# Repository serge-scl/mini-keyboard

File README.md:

# Mouse Keyboard Pyramids (MKP)

Hybrid mouse + keyboard using pyramid-shaped touch/tilt keys. MKP combines capacitive touch, tilt sensing, and small-form HID firmware to provide an alternative input device for typing and pointing.

## Features
- Pyramid-shaped keys: touch shows cursor location; tilt selects symbols/directions.
- Position sensing: MPR121 capacitive touch controller (per-pyramid address).
- Tilt sensing: magnet-mounted mesh + Hall sensors detect X/Y tilt.
- Keyboard: 5×3 matrix (with diodes) + two dedicated joystick inputs.
- Pointing: optional optical sensor (PMW3360) and two side scroll wheels (one per side).
- Modular hardware: removable side modules with 4×AA battery holders and PCBs; LED backlight PCB under keyboard.
- Assembly designed for minimal tools; partly tool-free disassembly.
- Wireless option: Raspberry Pi Pico (or Pico W for Wi‑Fi); CircuitPython with Adafruit libraries and HID support.

## Software & Files
- CircuitPython code and example text editor included in repo root (Python).
- FreeCAD (part/assembly) models and KiCad schematics/PCB in respective folders.
- Datasheet folder contains BOM, diagrams, and images.

## License
CC‑BY‑4.0

## Contact
Serge Sokolov — sergesclv@gmail.com / sergesclv3@protonmail.com

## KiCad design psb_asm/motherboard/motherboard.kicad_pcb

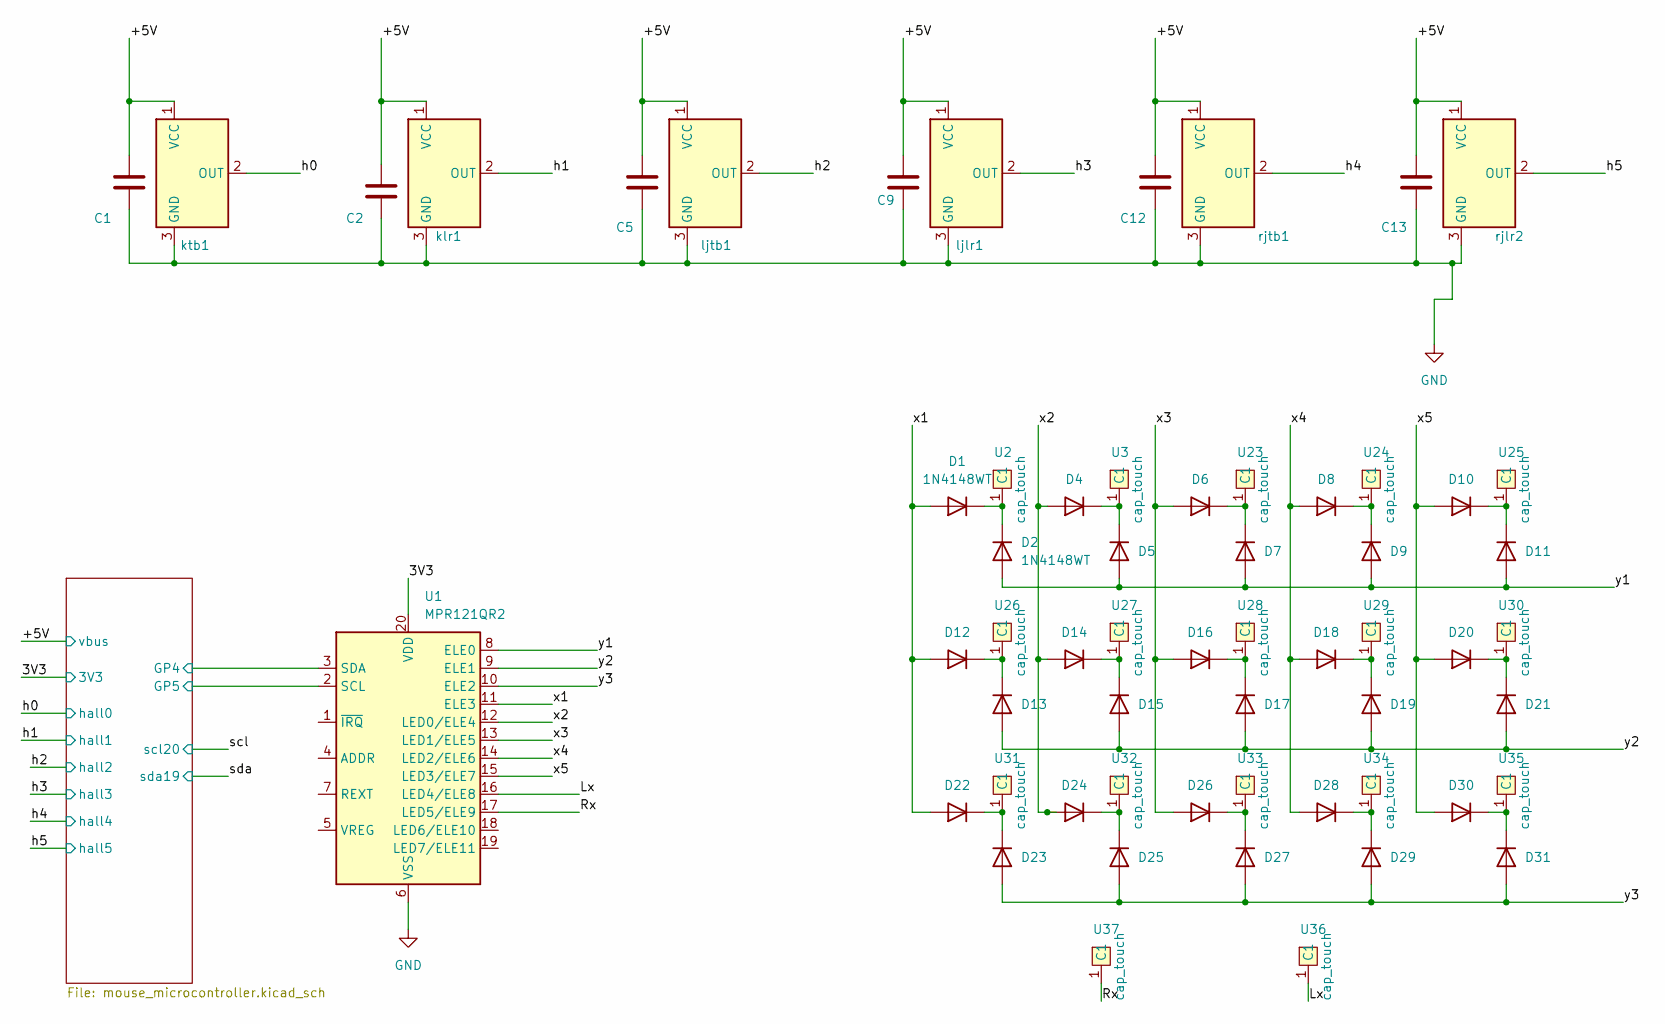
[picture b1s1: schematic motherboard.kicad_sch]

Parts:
C1, C2, C5, C9, C12, C13: 0.01uf; CP_EIA-1608-08_AVX-J_Pad1.25x1.05mm_HandSolder
D1, D2, D4, D5, D6, D7, D8, D9, D10, D11, D12, D13, D14, D15, D16, D17, D18, D19, D20, D21, D22, D23, D24, D25, D26, D27, D28, D29, D30, D31: 1N4148WT; D_SOD-523
U1: MPR121QR2; UQFN-20_3x3mm_P0.4mm
U2, U3, U23, U24, U25, U26, U27, U28, U29, U30, U31, U32, U33, U34, U35, U36, U37: cap_touch
klr1: TO-92S
ktb1: TO-92S
ljlr1: DRV505; TO-92S
ljtb1: DRV505; TO-92S
rjlr2: DRV505; TO-92S
rjtb1: DRV505; TO-92S

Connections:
/3V3: U1.20 (VDD); also elsewhere on the board
/+5V: C1.1, C2.1, C5.1, C9.1, C12.1, C13.1, klr1.1 (VCC), ktb1.1 (VCC), ljlr1.1 (VCC), ljtb1.1 (VCC), rjlr2.1 (VCC), rjtb1.1 (VCC); also elsewhere on the board
/Lx: U1.16 (LED4/ELE8), U36.1 (C1)
/Mouse_and_microcontroller/GP4: U1.3 (SDA); also elsewhere on the board
/Mouse_and_microcontroller/GP5: U1.2 (SCL); also elsewhere on the board
/Rx: U1.17 (LED5/ELE9), U37.1 (C1)
/h0: ktb1.2 (OUT); also elsewhere on the board
/h1: klr1.2 (OUT); also elsewhere on the board
/h2: ljtb1.2 (OUT); also elsewhere on the board
/h3: ljlr1.2 (OUT); also elsewhere on the board
/h4: rjtb1.2 (OUT); also elsewhere on the board
/h5: rjlr2.2 (OUT); also elsewhere on the board
/x1: D1.2 (A), D12.2 (A), D22.2 (A), U1.11 (ELE3)
/x2: D4.2 (A), D14.2 (A), D24.2 (A), U1.12 (LED0/ELE4)
/x3: D6.2 (A), D16.2 (A), D26.2 (A), U1.13 (LED1/ELE5)
/x4: D8.2 (A), D18.2 (A), D28.2 (A), U1.14 (LED2/ELE6)
/x5: D10.2 (A), D20.2 (A), D30.2 (A), U1.15 (LED3/ELE7)
/y1: D2.2 (A), D5.2 (A), D7.2 (A), D9.2 (A), D11.2 (A), U1.8 (ELE0)
/y2: D13.2 (A), D15.2 (A), D17.2 (A), D19.2 (A), D21.2 (A), U1.9 (ELE1)
/y3: D23.2 (A), D25.2 (A), D27.2 (A), D29.2 (A), D31.2 (A), U1.10 (ELE2)
GND: C1.2, C2.2, C5.2, C9.2, C12.2, C13.2, U1.6 (VSS), klr1.3 (GND), ktb1.3 (GND), ljlr1.3 (GND), ljtb1.3 (GND), rjlr2.3 (GND), rjtb1.3 (GND); also elsewhere on the board
unnamed: D1.1 (K), D2.1 (K), U2.1 (C1)
unnamed: D4.1 (K), D5.1 (K), U3.1 (C1)
unnamed: D6.1 (K), D7.1 (K), U23.1 (C1)
unnamed: D8.1 (K), D9.1 (K), U24.1 (C1)
unnamed: D10.1 (K), D11.1 (K), U25.1 (C1)
unnamed: D12.1 (K), D13.1 (K), U26.1 (C1)
unnamed: D14.1 (K), D15.1 (K), U27.1 (C1)
unnamed: D16.1 (K), D17.1 (K), U28.1 (C1)
unnamed: D18.1 (K), D19.1 (K), U29.1 (C1)
unnamed: D20.1 (K), D21.1 (K), U30.1 (C1)
unnamed: D22.1 (K), D23.1 (K), U31.1 (C1)
unnamed: D24.1 (K), D25.1 (K), U32.1 (C1)
unnamed: D26.1 (K), D27.1 (K), U33.1 (C1)
unnamed: D28.1 (K), D29.1 (K), U34.1 (C1)
unnamed: D30.1 (K), D31.1 (K), U35.1 (C1)

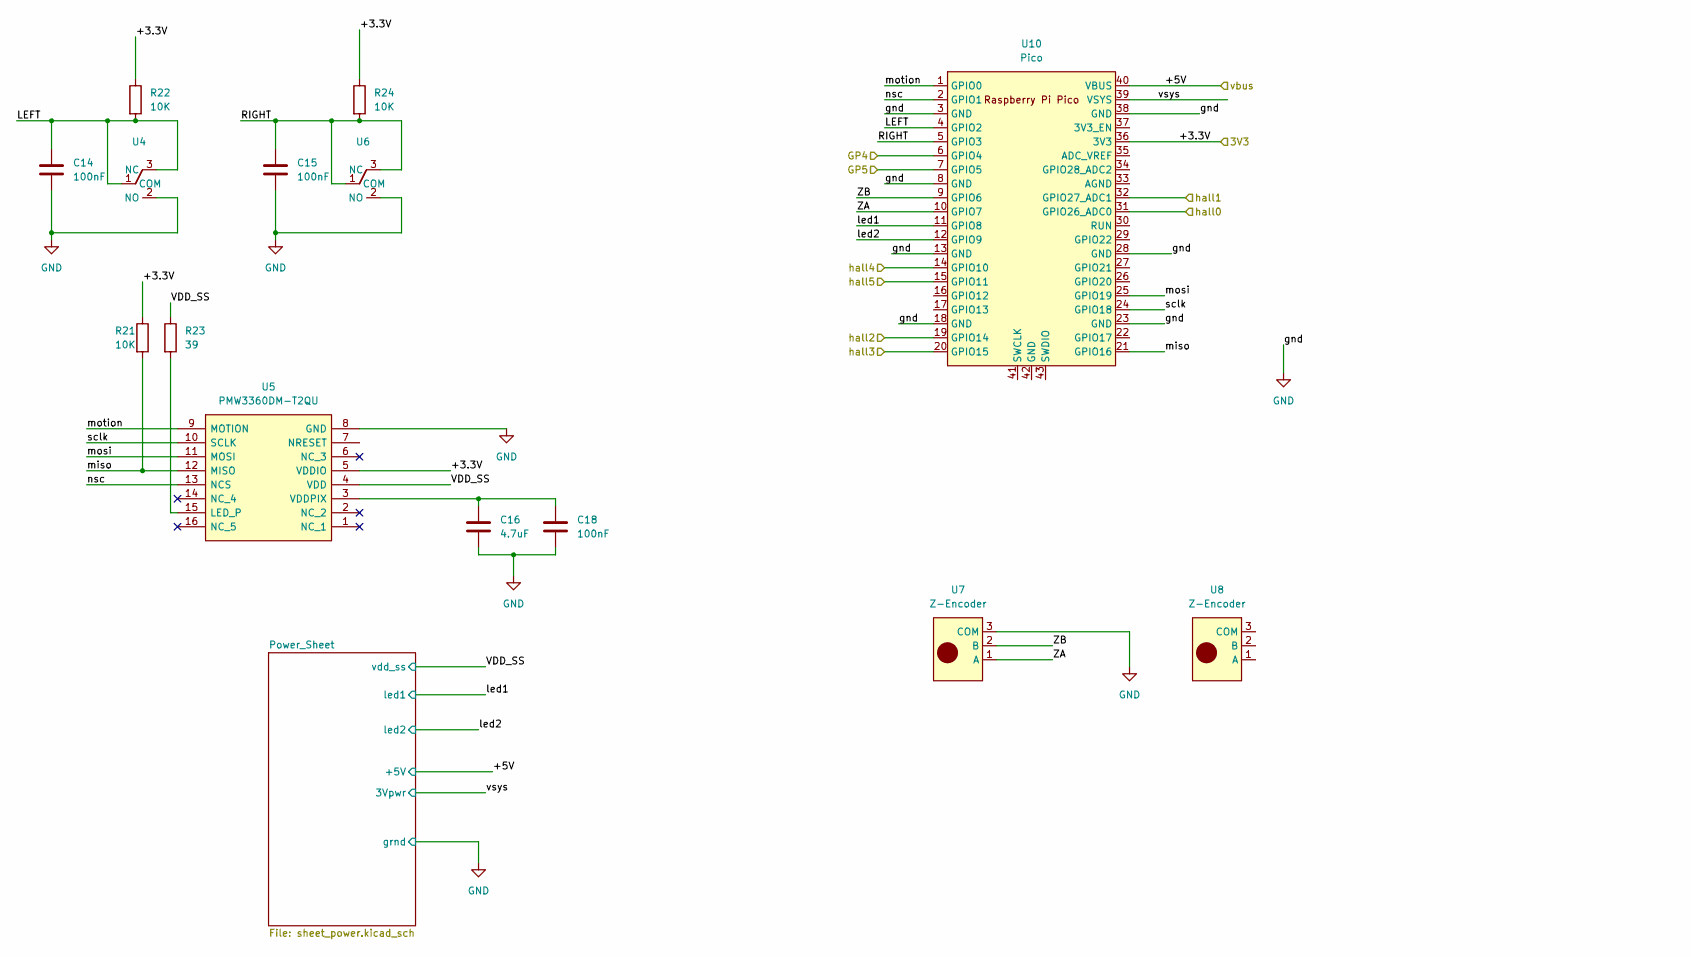
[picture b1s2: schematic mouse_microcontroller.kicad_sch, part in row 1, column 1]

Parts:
C14, C15: 100nF; CP_EIA-1608-08_AVX-J
C16: 4.7uF; CP_EIA-3216-12_Kemet-S_Pad1.58x1.35mm_HandSolder
C18: 100nF; CP_EIA-3216-12_Kemet-S_Pad1.58x1.35mm_HandSolder
R21: 10K; R_0402_1005Metric_Pad0.72x0.64mm_HandSolder
R22, R24: 10K; R_0603_1608Metric_Pad0.98x0.95mm_HandSolder
R23: 39; R_0402_1005Metric_Pad0.72x0.64mm_HandSolder
U4, U6: Switch; switch
U5: PMW3360DM-T2QU; PMW3360; Manufacturer_Part_Number PMW3360DM-T2QU
U7, U8: Z-Encoder
U10: Pico; RPi_Pico_SMD_TH

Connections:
/3V3: R21.1, R22.1, R24.1, U5.5 (VDDIO), U10.36 (3V3); also elsewhere on the board
/+5V: U10.40 (VBUS); also elsewhere on the board
/Mouse_and_microcontroller/GP4: U10.6 (GPIO4); also elsewhere on the board
/Mouse_and_microcontroller/GP5: U10.7 (GPIO5); also elsewhere on the board
/Mouse_and_microcontroller/LEFT: C14.1, R22.2, U4.1 (COM), U4.3 (NC), U10.4 (GPIO2)
/Mouse_and_microcontroller/RIGHT: C15.1, R24.2, U6.1 (COM), U6.3 (NC), U10.5 (GPIO3)
/Mouse_and_microcontroller/VDD_SS: R23.1, U5.4 (VDD); also elsewhere on the board
/Mouse_and_microcontroller/ZA: U7.1 (A), U10.10 (GPIO7)
/Mouse_and_microcontroller/ZB: U7.2 (B), U10.9 (GPIO6)
/Mouse_and_microcontroller/led1: U10.11 (GPIO8); also elsewhere on the board
/Mouse_and_microcontroller/led2: U10.12 (GPIO9); also elsewhere on the board
/Mouse_and_microcontroller/miso: R21.2, U5.12 (MISO), U10.21 (GPIO16)
/Mouse_and_microcontroller/mosi: U5.11 (MOSI), U10.25 (GPIO19)
/Mouse_and_microcontroller/motion: U5.9 (MOTION), U10.1 (GPIO0)
/Mouse_and_microcontroller/nsc: U5.13 (NCS), U10.2 (GPIO1)
/Mouse_and_microcontroller/sclk: U5.10 (SCLK), U10.24 (GPIO18)
/Mouse_and_microcontroller/vsys: U10.39 (VSYS); also elsewhere on the board
/h0: U10.31 (GPIO26_ADC0); also elsewhere on the board
/h1: U10.32 (GPIO27_ADC1); also elsewhere on the board
/h2: U10.19 (GPIO14); also elsewhere on the board
/h3: U10.20 (GPIO15); also elsewhere on the board
/h4: U10.14 (GPIO10); also elsewhere on the board
/h5: U10.15 (GPIO11); also elsewhere on the board
GND: C14.2, C15.2, C16.2, C18.2, U4.2 (NO), U5.8 (GND), U6.2 (NO), U7.3 (COM), U10.3 (GND), U10.8 (GND), U10.13 (GND), U10.18 (GND), U10.23 (GND), U10.28 (GND), U10.38 (GND); also elsewhere on the board
unnamed: R23.2, U5.15 (LED_P)
unnamed: C16.1, C18.1, U5.3 (VDDPIX)

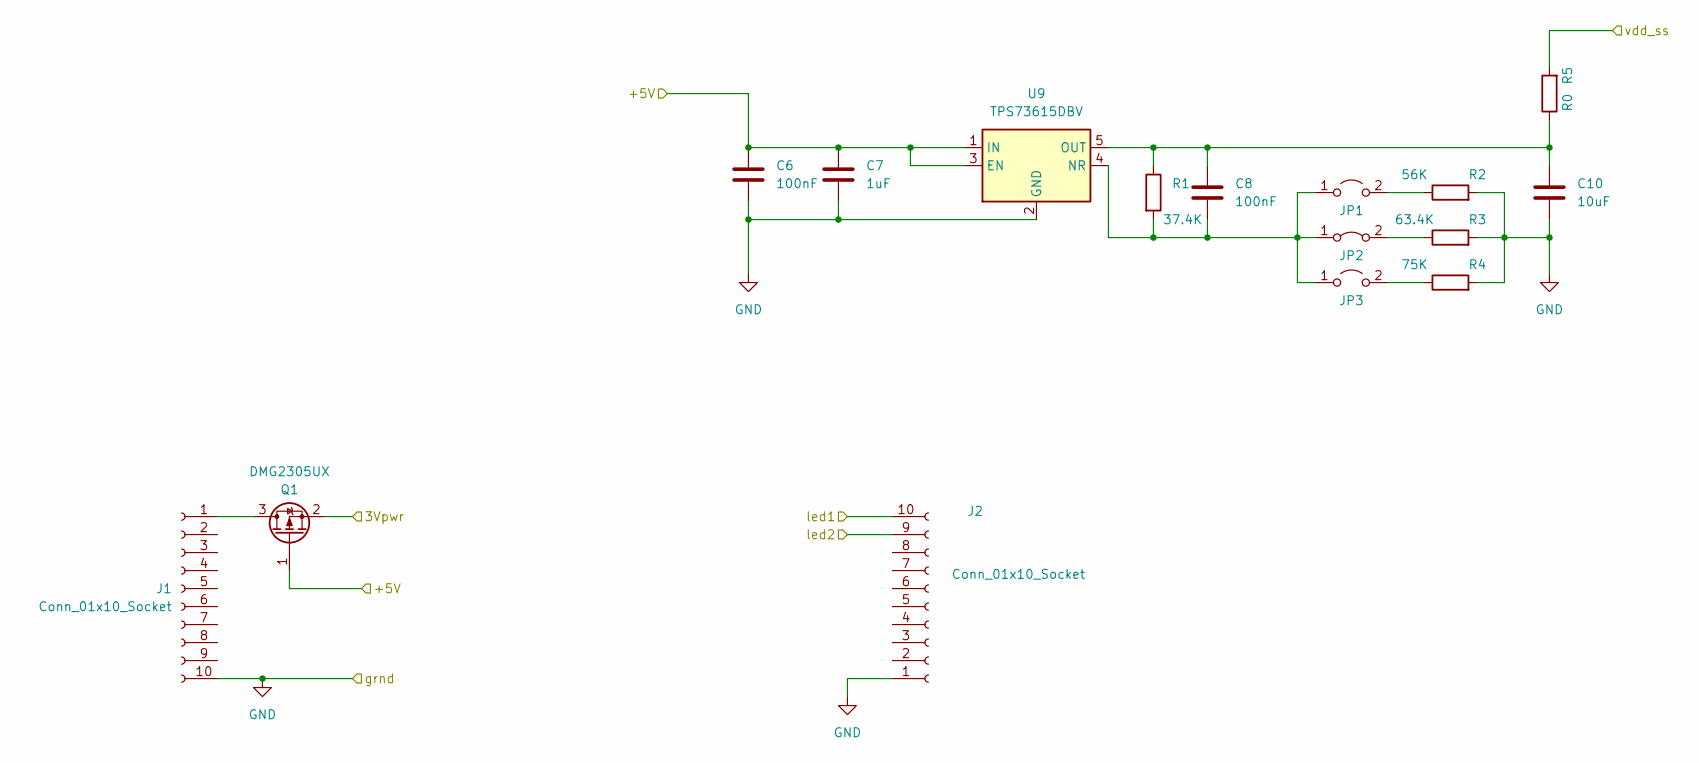
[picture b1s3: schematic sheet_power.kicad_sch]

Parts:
C6, C8: 100nF; CP_EIA-1608-08_AVX-J
C7: 1uF; CP_EIA-1608-08_AVX-J
C10: 10uF; CP_EIA-1608-08_AVX-J
J1, J2: Conn_01x10_Socket; BF088
JP1, JP3: Jumper_2_Open; jump_off
JP2: Jumper_2_Bridged; Jump_on
Q1: DMG2305UX; SOT-23
R1: 37.4K; R_0603_1608Metric
R2: 56K; R_0603_1608Metric
R3: 63.4K; R_0603_1608Metric
R4: 75K; R_0603_1608Metric
R5: R0; R_0603_1608Metric
U9: TPS73615DBV; SOT-23-5

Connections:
/+5V: C6.1, C7.1, Q1.1 (G), U9.1 (IN), U9.3 (EN); also elsewhere on the board
/Mouse_and_microcontroller/VDD_SS: R5.2; also elsewhere on the board
/Mouse_and_microcontroller/led1: J2.10; also elsewhere on the board
/Mouse_and_microcontroller/led2: J2.9; also elsewhere on the board
/Mouse_and_microcontroller/vsys: Q1.2 (S); also elsewhere on the board
GND: C6.2, C7.2, C10.2, J1.10, J2.1, R2.2, R3.2, R4.2, U9.2 (GND); also elsewhere on the board
unnamed: J1.1, Q1.3 (D)
unnamed: C8.2, JP1.1 (A), JP2.1 (A), JP3.1 (A), R1.2, U9.4 (NR)
unnamed: JP1.2 (B), R2.1
unnamed: JP2.2 (B), R3.1
unnamed: JP3.2 (B), R4.1
unnamed: C8.1, C10.1, R1.1, R5.1, U9.5 (OUT)

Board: 2 copper layers, 90 parts (39 on the bottom side), 57 nets, no tracks yet.

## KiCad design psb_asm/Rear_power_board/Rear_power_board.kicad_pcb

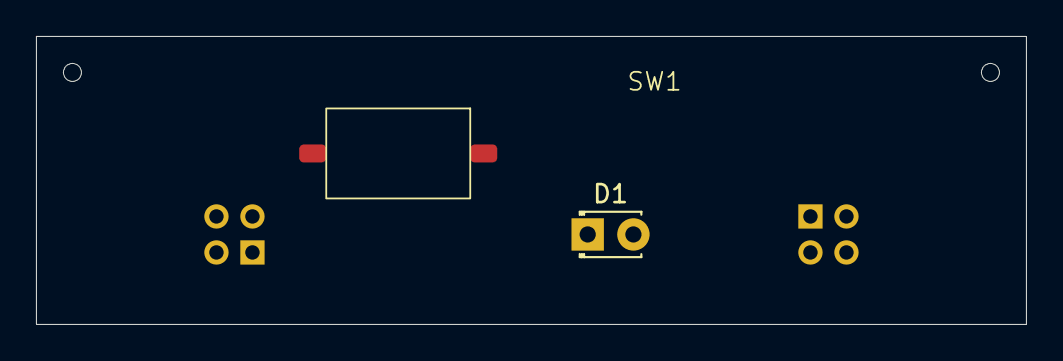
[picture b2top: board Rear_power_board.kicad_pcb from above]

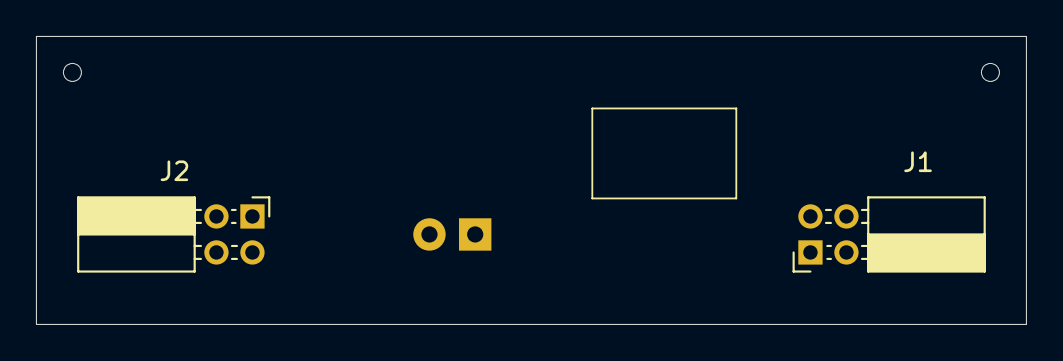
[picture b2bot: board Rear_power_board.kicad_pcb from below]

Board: 2 copper layers, 55.0 x 16.0 mm, 4 parts (2 on the bottom side), 2 nets, no tracks yet.

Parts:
D1: LED; LED_D1.8mm_W3.3mm_H2.4mm
J1, J2: Conn_01x04_Socket; PinSocket_2x02_P2.00mm_Horizontal
SW1: SW_DIP_x01; switch_pw

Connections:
unnamed: D1.2 (A), J2.3, SW1.2
unnamed: J1.1, J2.4, SW1.1

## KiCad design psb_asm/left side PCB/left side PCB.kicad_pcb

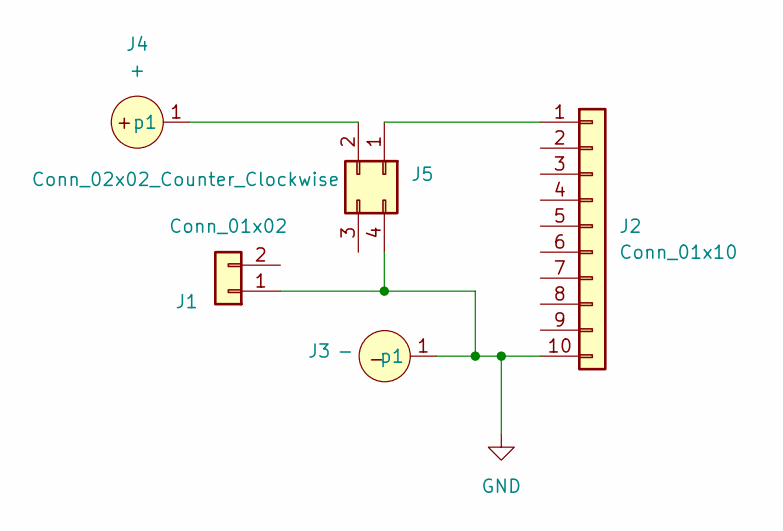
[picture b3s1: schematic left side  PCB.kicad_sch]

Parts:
J1: Conn_01x02; PinHeader_1x02_P2.00mm_Vertical
J2: Conn_01x10; PinHeader_1x10_P2.00mm_Vertical
J3: -; batter_conn
J4: +; batter_conn
J5: Conn_02x02_Counter_Clockwise; PinHeader_2x02_P2.00mm_Vertical

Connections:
GND: J1.1, J2.10, J3.1 (p1), J5.4
unnamed: J2.1, J5.1
unnamed: J4.1 (p1), J5.2

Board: 2 copper layers, 5 parts (0 on the bottom side), 3 nets, no tracks yet.

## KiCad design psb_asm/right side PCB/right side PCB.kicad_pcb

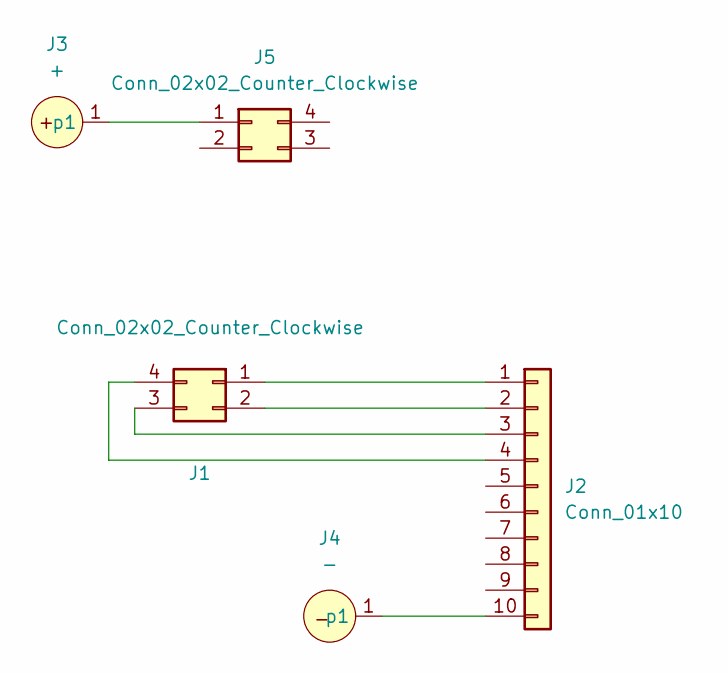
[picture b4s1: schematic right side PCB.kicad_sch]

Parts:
J1, J5: Conn_02x02_Counter_Clockwise; PinHeader_2x02_P2.00mm_Vertical
J2: Conn_01x10; PinHeader_1x10_P2.00mm_Vertical
J3: +; batter_conn
J4: -; batter_conn

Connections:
unnamed: J1.1, J2.1
unnamed: J1.2, J2.2
unnamed: J1.3, J2.3
unnamed: J1.4, J2.4
unnamed: J2.10, J4.1 (p1)
unnamed: J3.1 (p1), J5.1

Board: 2 copper layers, 5 parts (0 on the bottom side), 6 nets, no tracks yet.

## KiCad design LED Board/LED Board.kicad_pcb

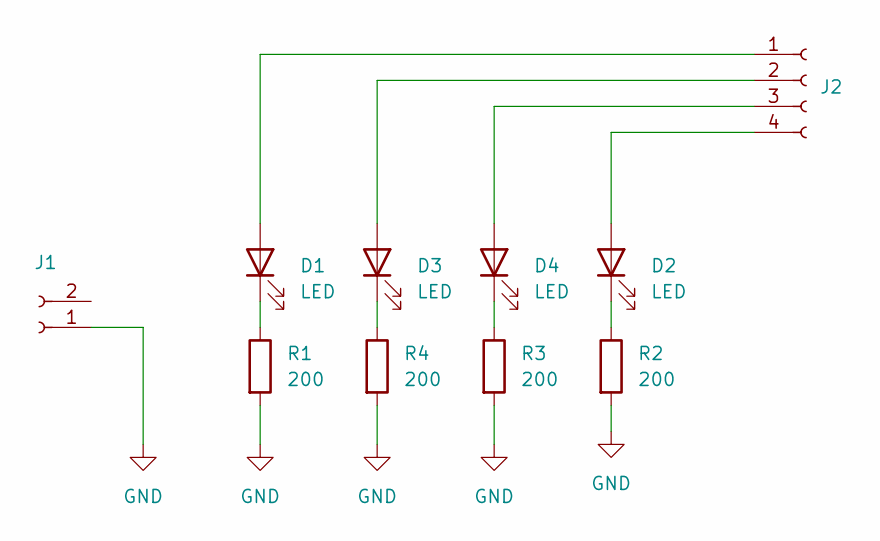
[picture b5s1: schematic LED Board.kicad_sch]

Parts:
D1, D2, D3, D4: LED; LED_PLCC_2835
J1: BF086
J2: PinSocket_2x02_P2.00mm_Horizontal
R1, R2, R3, R4: 200; RC0402N_PAN

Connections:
GND: J1.1, R1.2, R2.2, R3.2, R4.2
unnamed: D1.2 (A), J2.1
unnamed: D1.1 (K), R1.1
unnamed: D2.2 (A), J2.4
unnamed: D2.1 (K), R2.1
unnamed: D3.2 (A), J2.2
unnamed: D3.1 (K), R4.1
unnamed: D4.2 (A), J2.3
unnamed: D4.1 (K), R3.1

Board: 2 copper layers, 10 parts (6 on the bottom side), 9 nets, no tracks yet.

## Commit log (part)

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2019-09-18 Start act track
2019-09-30 correct input
2019-10-04 shift keyboard
2019-10-05 errors frequencly
2019-10-05 errors index
2019-10-12 short send 1,1 cut
2019-10-12 short send 1,1 cut + send
2023-03-25 Update README.txt
    cleaning
2023-03-26 cap and touch
2023-03-26 sensor details
2023-03-26 assemblys
2023-03-27 new parts and asm
2023-03-27 main rod
2023-03-28 button mechanism
2023-03-28 mezzonin
2023-03-29 sliding mesh and joystic
2023-03-30 keyboard module
2023-03-30 kicad
2023-03-31 bottom and walls
2023-03-31 kicad pro
2023-04-01 fin adding part files
2023-04-01 main module
2023-04-03 datasheet
2023-04-05 readme
2023-04-10 old code cut
2023-04-10 adafruit hid
2023-04-13 fix error hall
2023-04-24 led board
2023-04-24 led fix error
2023-04-25 led pyramid module
2023-04-26 pcbasm tree
2023-05-01 conn plug battery
2023-05-06 fix plug battr
2023-05-07 delet rings
2023-05-08 ,attry connectors
2023-05-17 side pcb
2023-05-17 battery wall r asm
2023-05-19 middle connect
2023-05-24 conn in mother 5
2023-05-25 right conn mother
2023-05-30 conn side led
2023-06-10 add led conn pcb
2023-06-12 correct conn led
2023-06-16 motherboard conn
2023-06-22 power end
2023-07-04 new sensor
2023-07-10 newsnsspring
2023-07-13 grill sockt
2023-07-16 new asm sns
2023-07-17 wall left right
2023-07-22 3dmother
2023-07-24 mkp new
2023-07-24 bom dell1
2023-07-25 mkp2 del8
2023-07-30 motherboard2
2023-07-31 cap nich
2023-08-03 top lock
2023-08-03 cjver stock
2023-08-04 mkp 1d2m
2023-08-04 dell hall
2023-08-21 screen keyboard
2023-08-22 delet old staff
2023-08-25 delrt tree md bom
2023-09-04 event kb
2023-09-07 event2
2023-09-08 event3
2023-09-10 event_greed
2023-09-11 ev_grd2
2023-09-22 code pico
2023-09-24 all keyboard
2023-09-24 mkps
2023-10-05 full kb
2023-10-08 text editor
2023-11-15 hall sensor
2023-11-16 cp10 to A0
2023-11-24 oh49e
2023-11-25 mpr121
2023-11-27 diodes
2023-11-29 motherboard
2023-11-30 sensor touch
2023-12-01 mpr121 datashit
2023-12-05 magnet holders
2023-12-12 bom new
2023-12-21 spring clcpw
2023-12-22 bom add
2024-01-02 link wk
2024-01-07 nhstruct
2024-05-10 new branch
2024-05-12 spring x
2024-05-13 bracet
2024-05-13 spring asm
2024-05-24 spring01mm
2024-05-27 top spring
2024-06-10 bom10624
2024-06-12 tvent t e
2024-06-16 altctrl
2024-06-18 kikad te
2024-06-21 t-e#x
2024-06-26 pressrelis
2024-07-02 kicad8
2024-08-28 txttomd
2024-10-30 wiwatspring
2024-11-02 delold2mesh
2024-11-03 readme2
2024-11-04 clearrm
2024-11-06 picttditir
2024-11-09 bomnew
2024-11-11 red plugin
2024-12-02 skel_bn
2024-12-18 connbatr
2024-12-24 pcbaxis
2024-12-29 mothrboard_ft
2025-01-02 deviseallasm
2025-01-05 conLedPCB
2025-01-09 led2connLR
2025-01-13 boxpcb
2025-01-19 datasht
2025-02-01 backpcb
2025-02-04 resistorled
2025-02-23 newjoystic
2025-04-07 restart
2025-04-10 bom100325
2025-04-25 delettip
2025-05-28 two_will
2025-06-05 pic16f
2026-02-15 asm_pcb
2026-06-22 Create CNAME
2026-06-23 index_file
2026-06-28 Modernize index.html: add title, semantic structure, responsive image and alt text
2026-06-28 mkps_new_text
2026-06-29 image_Tuluse_Lotreck
